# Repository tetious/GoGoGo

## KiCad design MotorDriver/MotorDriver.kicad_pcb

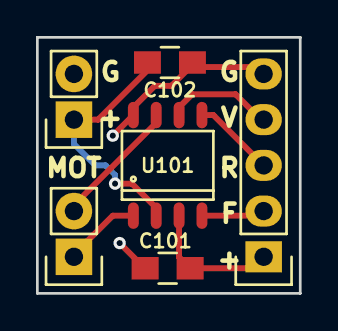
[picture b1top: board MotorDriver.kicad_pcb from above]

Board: 2 copper layers, 14.6 x 14.2 mm, 6 parts (0 on the bottom side), 8 nets.

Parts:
C101: 1uf; C_0805_HandSoldering
C102: 10uf; C_0805_HandSoldering
P101: CONTROL; Pin_Header_Straight_1x05
P102: MOT; Pin_Header_Straight_1x02
P103: Vm; Pin_Header_Straight_1x02
U101: ZXBM5210; SO-8

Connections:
GND: C101.1, C102.1, P101.5, P103.2, U101.8
unnamed: C102.2, P103.1, U101.2
unnamed: P101.2, U101.4
unnamed: P101.3, U101.5
unnamed: P101.4, U101.6
unnamed: P102.1, U101.1
unnamed: P102.2, U101.7
Vdd: C101.2, P101.1, U101.3

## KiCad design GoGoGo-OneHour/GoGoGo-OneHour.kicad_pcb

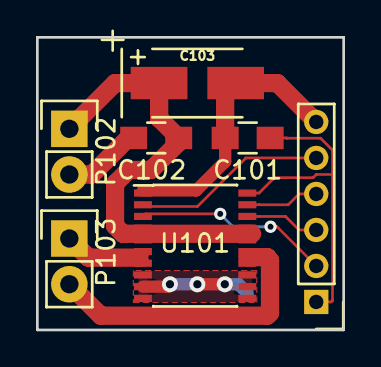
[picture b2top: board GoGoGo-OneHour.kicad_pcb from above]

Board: 2 copper layers, 17.0 x 16.3 mm, 7 parts (0 on the bottom side), 9 nets.

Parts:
C101, C102: .1uf; C_0805_HandSoldering
C103: 10uf; TantalC_SizeB_EIA-3528_HandSoldering
P101: CONTROL; Pin_Header_Straight_1x06_Pitch2.00mm
P102: VM; Pin_Header_Straight_1x02
P103: MOT; Pin_Header_Straight_1x02
U101: TB6593FNG; SSOP-20_4.4x6.5mm_Pitch0.65mm

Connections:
/O1: P103.1, U101.6, U101.7
/O2: P103.2, U101.14, U101.15
/VCC: C101.2, P101.1, U101.20
/VM+: C102.2, C103.1, P102.1, U101.4, U101.5, U101.16, U101.17
GND: C101.1, C102.1, C103.2, P101.6, P102.2, U101.1, U101.8, U101.9, U101.10, U101.11, U101.12, U101.13
unnamed: P101.2, U101.3
unnamed: P101.3, U101.18
unnamed: P101.4, U101.19
unnamed: P101.5, U101.2

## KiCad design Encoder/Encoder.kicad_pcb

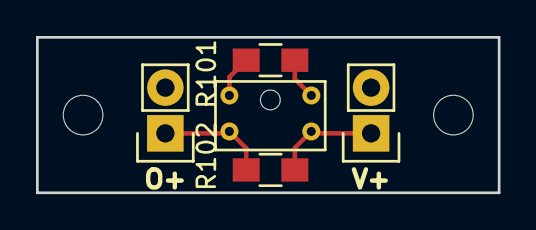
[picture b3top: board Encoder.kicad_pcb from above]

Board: 2 copper layers, 25.7 x 8.6 mm, 5 parts (0 on the bottom side), 4 nets.

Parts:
P101: VCC; Pin_Header_Straight_1x02
P102: OPTO; Pin_Header_Straight_1x02
R101: 100; R_0805_HandSoldering
R102: 10k; R_0805_HandSoldering
U101: GP1S094HCZ0F

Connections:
GND: P101.2, P102.2, R101.2, U101.3
unnamed: P102.1, R102.2, U101.2
unnamed: R101.1, U101.4
VCC: P101.1, R102.1, U101.1

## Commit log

2016-08-06 Initial checkin.
2016-08-14 Clean up motor driver board.
2016-08-14 Cleanups.
